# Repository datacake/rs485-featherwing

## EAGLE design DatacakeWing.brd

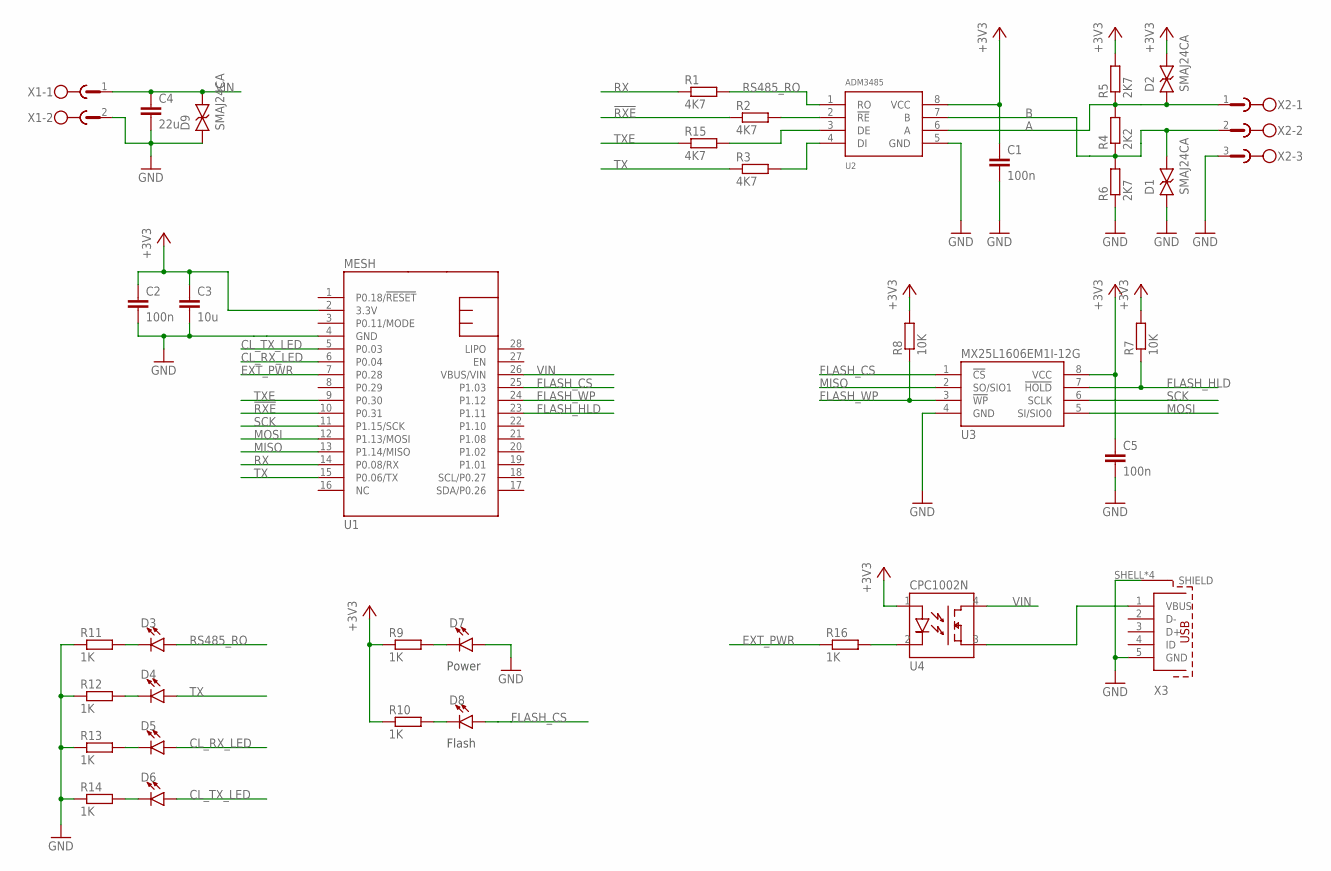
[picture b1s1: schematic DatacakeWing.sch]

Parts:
C1, C2, C5: 100n; C0603
C3: 10u; C0603
C4: 22u; C1210
D1, D2, D9: SMAJ24CA; DO-214AC
D3, D4, D5, D6, D7, D8: LED0603; LED-0603
R1, R2, R3, R15: 4K7; R0402
R4: 2K2; R0402
R5, R6: 2K7; R0402
R7, R8: 10K; R0402
R9, R10, R11, R12, R13, R14, R16: 1K; R0402
U1: MESH; FEATHERWING
U2: ADM3485; SO08-0.15
U3: MX25L1606EM1I-12G; SO08-0.15
U4: CPC1002N
X1: MC1,5/2-G-3,5; MC-2
X2: MC1,5/3-G-3,5; MC-3
X3: 629105136821

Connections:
!RXE: R2.1, U1.10 (P0.31)
+3V3: C1.1, C2.1, C3.1, C5.1, D2.2, R5.2, R7.2, R8.2, R9.1, R10.1, U1.2 (3.3V), U2.8 (VCC), U3.8 (VCC), U4.1
A: D2.1, R4.2, R5.1, U2.6 (A), X2.1
B: D1.2, R4.1, R6.2, U2.7 (B), X2.2
CL_RX_LED: D5.A, U1.6 (P0.04)
CL_TX_LED: D6.A, U1.5 (P0.03)
EXT_PWR: R16.1, U1.7 (P0.28)
FLASH_CS: D8.A, U1.25 (P1.03), U3.1 (!CS)
FLASH_HLD: R7.1, U1.23 (P1.11), U3.7 (!HOLD)
FLASH_WP: R8.1, U1.24 (P1.12), U3.3 (!WP)
GND: C1.2, C2.2, C3.2, C4.2, C5.2, D1.1, D7.A, D9.1, R6.1, R11.1, R12.1, R13.1, R14.1, U1.4 (GND), U2.5 (GND), U3.4 (GND), X1.2, X2.3, X3.5 (GND), X3.SHELL (SHIELD), X3.SHELL1 (SHIELD), X3.SHELL2 (SHIELD), X3.SHELL3 (SHIELD)
MISO: U1.13 (P1.14/MISO), U3.2 (SO/SIO1)
MOSI: U1.12 (P1.13/MOSI), U3.5 (SI/SIO0)
unnamed: R2.2, U2.2 (!RE)
unnamed: D3.C, R11.2
unnamed: R3.2, U2.4 (DI)
unnamed: D4.C, R12.2
unnamed: D5.C, R13.2
unnamed: D6.C, R14.2
unnamed: D7.C, R9.2
unnamed: R15.2, U2.3 (DE)
unnamed: D8.C, R10.2
unnamed: U4.3, X3.1 (VBUS)
unnamed: R16.2, U4.2
RS485_RO: D3.A, R1.2, U2.1 (RO)
RX: R1.1, U1.14 (P0.08/RX)
SCK: U1.11 (P1.15/SCK), U3.6 (SCLK)
TX: D4.A, R3.1, U1.15 (P0.06/TX)
TXE: R15.1, U1.9 (P0.30)
VIN: C4.1, D9.2, U1.26 (VBUS/VIN), U4.4, X1.1

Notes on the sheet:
Power
Flash

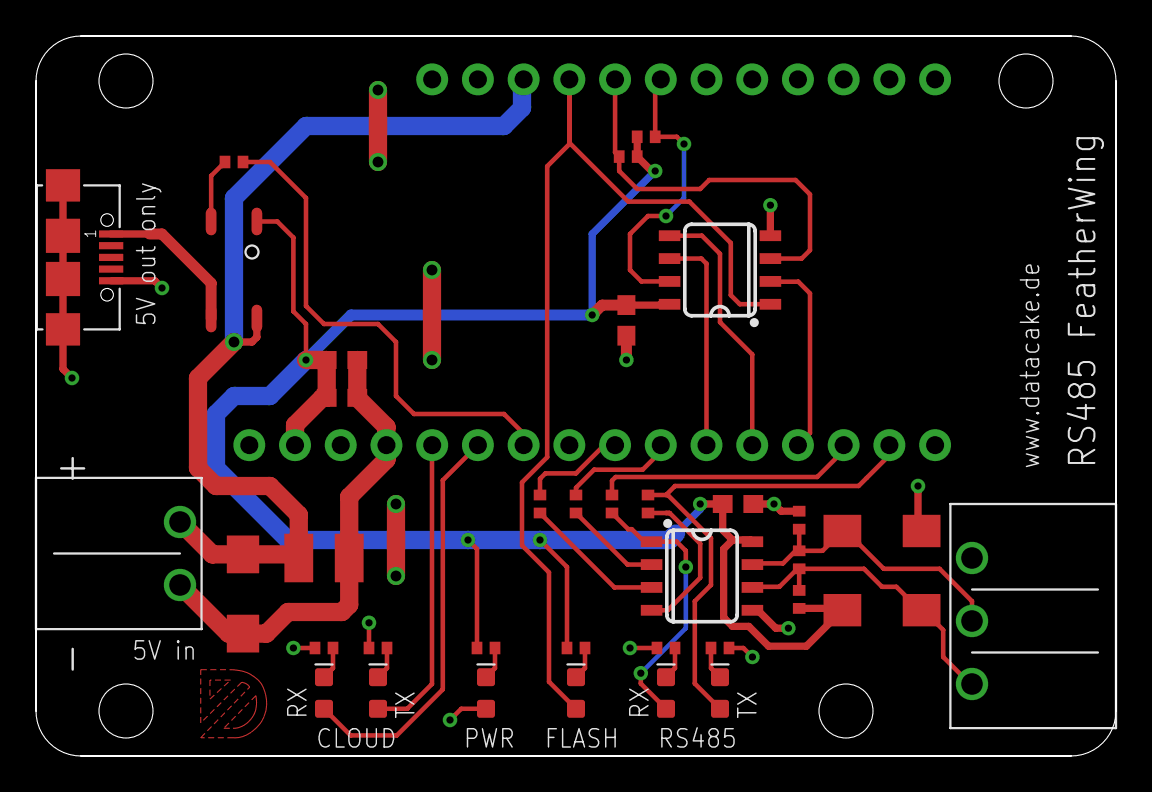
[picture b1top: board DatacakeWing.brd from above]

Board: 2 copper layers, 60.0 x 40.0 mm, 37 parts (0 on the bottom side), 30 nets.

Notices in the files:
parts and their libraries:
Particle-Devices: Licensing: Designed by Particle.
SparkFun-LED: Licensing: Creative Commons ShareAlike 4.0 International - https://creativecommons.org/licenses/by-sa/4.0
Wurth_Elektronik_Electromechanic_Input-O: Copyright: Würth Elektronik
